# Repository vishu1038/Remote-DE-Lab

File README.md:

# Remote-DE-Lab
Remote Digital Electronics Lab

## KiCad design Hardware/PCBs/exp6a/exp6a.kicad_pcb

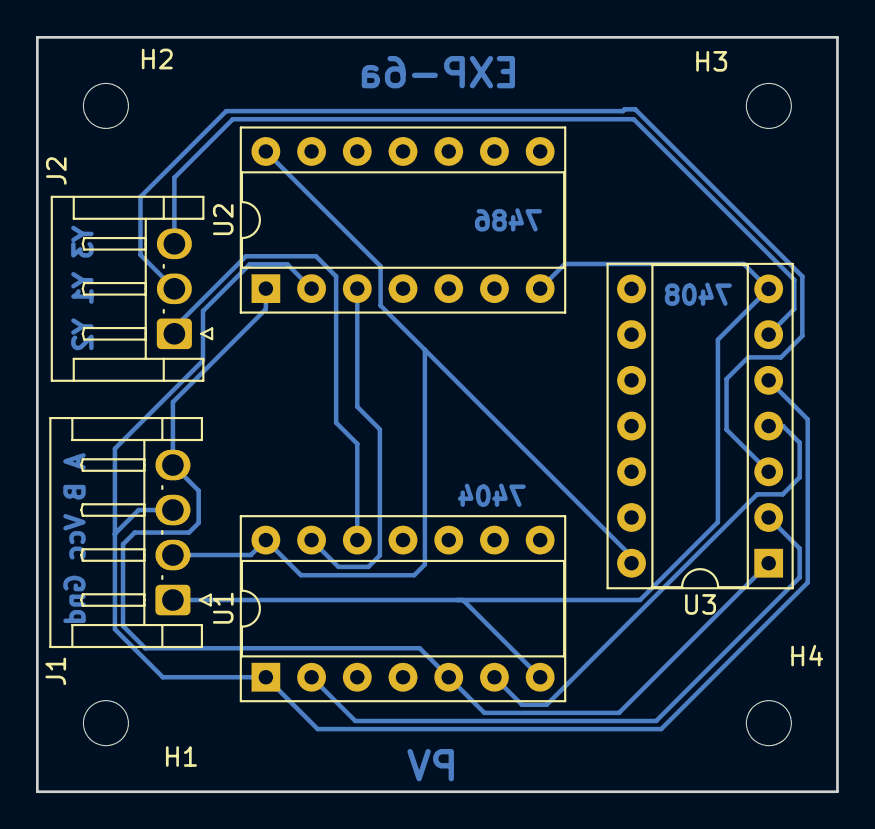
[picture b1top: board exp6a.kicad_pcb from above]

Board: 2 copper layers, 44.5 x 41.9 mm, 9 parts (0 on the bottom side), 10 nets.

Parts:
H1, H2, H3, H4: MountingHole; MountingHole_2.5mm
J1: A B Vcc Gnd; JST_EH_S4B-EH_1x04_P2.50mm_Horizontal
J2: Y3 Y1 Y2; JST_EH_S3B-EH_1x03_P2.50mm_Horizontal
U1: 7404; DIP-14_W7.62mm_Socket
U2: 7486; DIP-14_W7.62mm_Socket
U3: 7408; DIP-14_W7.62mm_Socket

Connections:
A: J1.4, U1.5, U2.1, U3.1
B: J1.3, U1.1, U2.2, U3.5
GND: J1.1, U1.7 (Gnd), U2.7 (Gnd), U3.7 (Gnd)
unnamed: U1.2, U3.2
unnamed: U1.6, U3.4
unnamed: U1.13, U2.3
VCC: J1.2, U1.14 (Vcc), U2.14 (Vcc), U3.14 (Vcc)
Y1: J2.2, U3.3
Y2: J2.1, U1.12
Y3: J2.3, U3.6

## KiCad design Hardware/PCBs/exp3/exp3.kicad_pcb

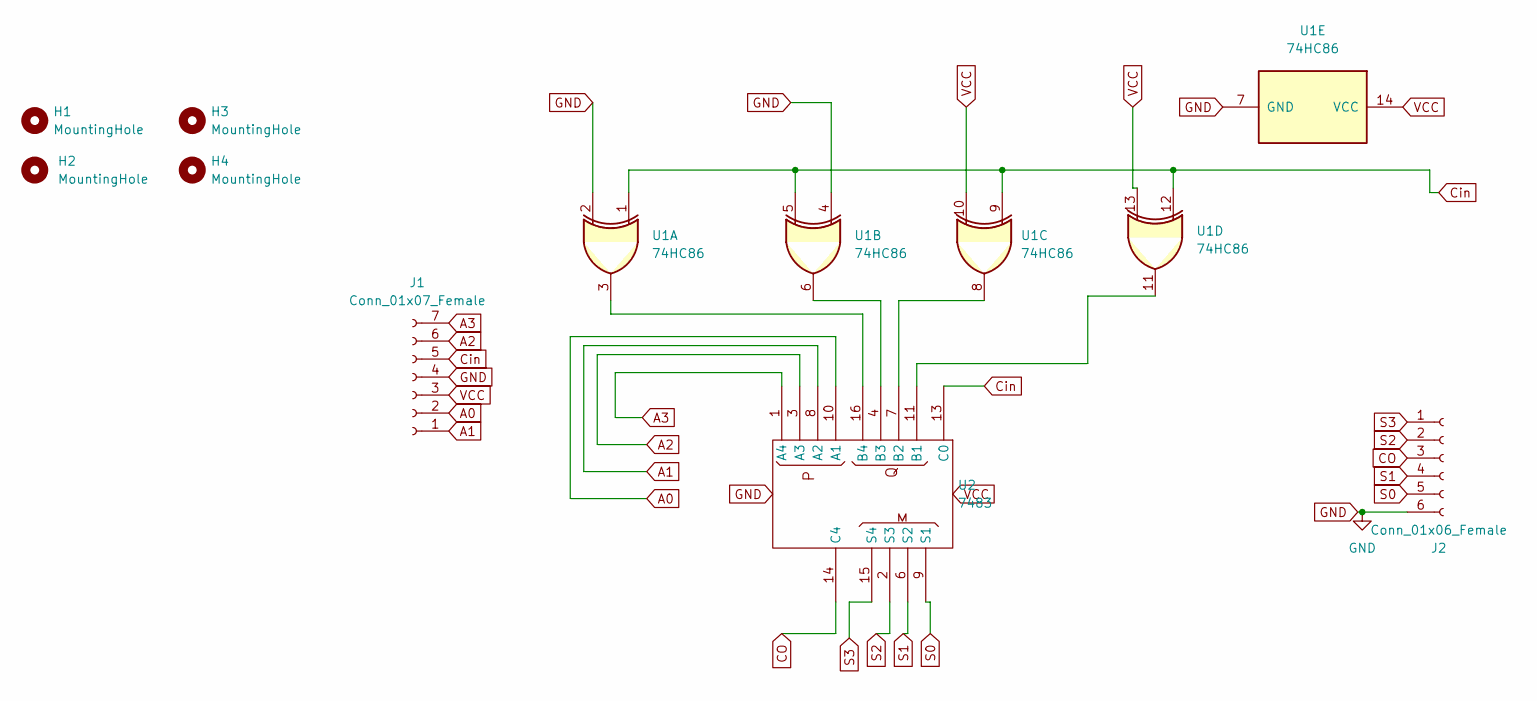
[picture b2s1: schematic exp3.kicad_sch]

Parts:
H1, H2, H3, H4: MountingHole; MountingHole_2.5mm
J1: Conn_01x07_Female; JST_EH_S7B-EH_1x07_P2.50mm_Horizontal
J2: Conn_01x06_Female; JST_EH_S6B-EH_1x06_P2.50mm_Horizontal
U1: 74HC86; DIP-14_W7.62mm_Socket
U2: 7483; DIP-16_W7.62mm_Socket

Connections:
A0: J1.2, U2.10 (A1)
A1: J1.1, U2.8 (A2)
A2: J1.6, U2.3 (A3)
A3: J1.7, U2.1 (A4)
CO: J2.3, U2.14 (C4)
Cin: J1.5, U1.1, U1.5, U1.9, U1.12, U2.13 (C0)
GND: J1.4, J2.6, U1.2, U1.4, U1.7 (GND), U2.12 (GND)
unnamed: U1.3, U2.16 (B4)
unnamed: U1.6, U2.4 (B3)
unnamed: U1.8, U2.7 (B2)
unnamed: U1.11, U2.11 (B1)
S0: J2.5, U2.9 (S1)
S1: J2.4, U2.6 (S2)
S2: J2.2, U2.2 (S3)
S3: J2.1, U2.15 (S4)
VCC: J1.3, U1.10, U1.13, U1.14 (VCC), U2.5 (VCC)

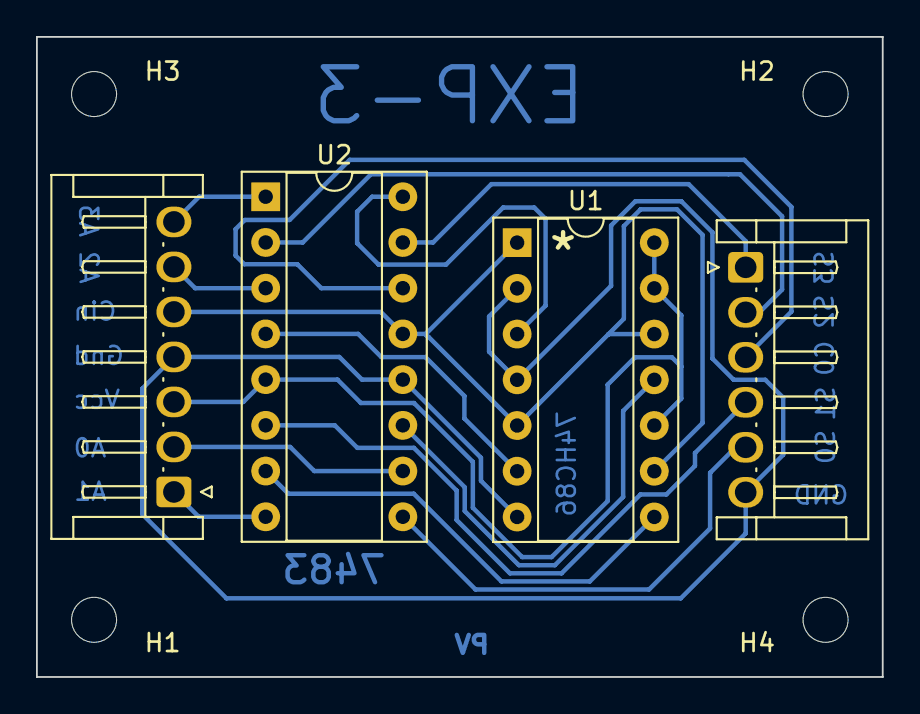
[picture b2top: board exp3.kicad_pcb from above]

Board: 2 copper layers, 47.0 x 35.6 mm, 8 parts (0 on the bottom side), 16 nets.

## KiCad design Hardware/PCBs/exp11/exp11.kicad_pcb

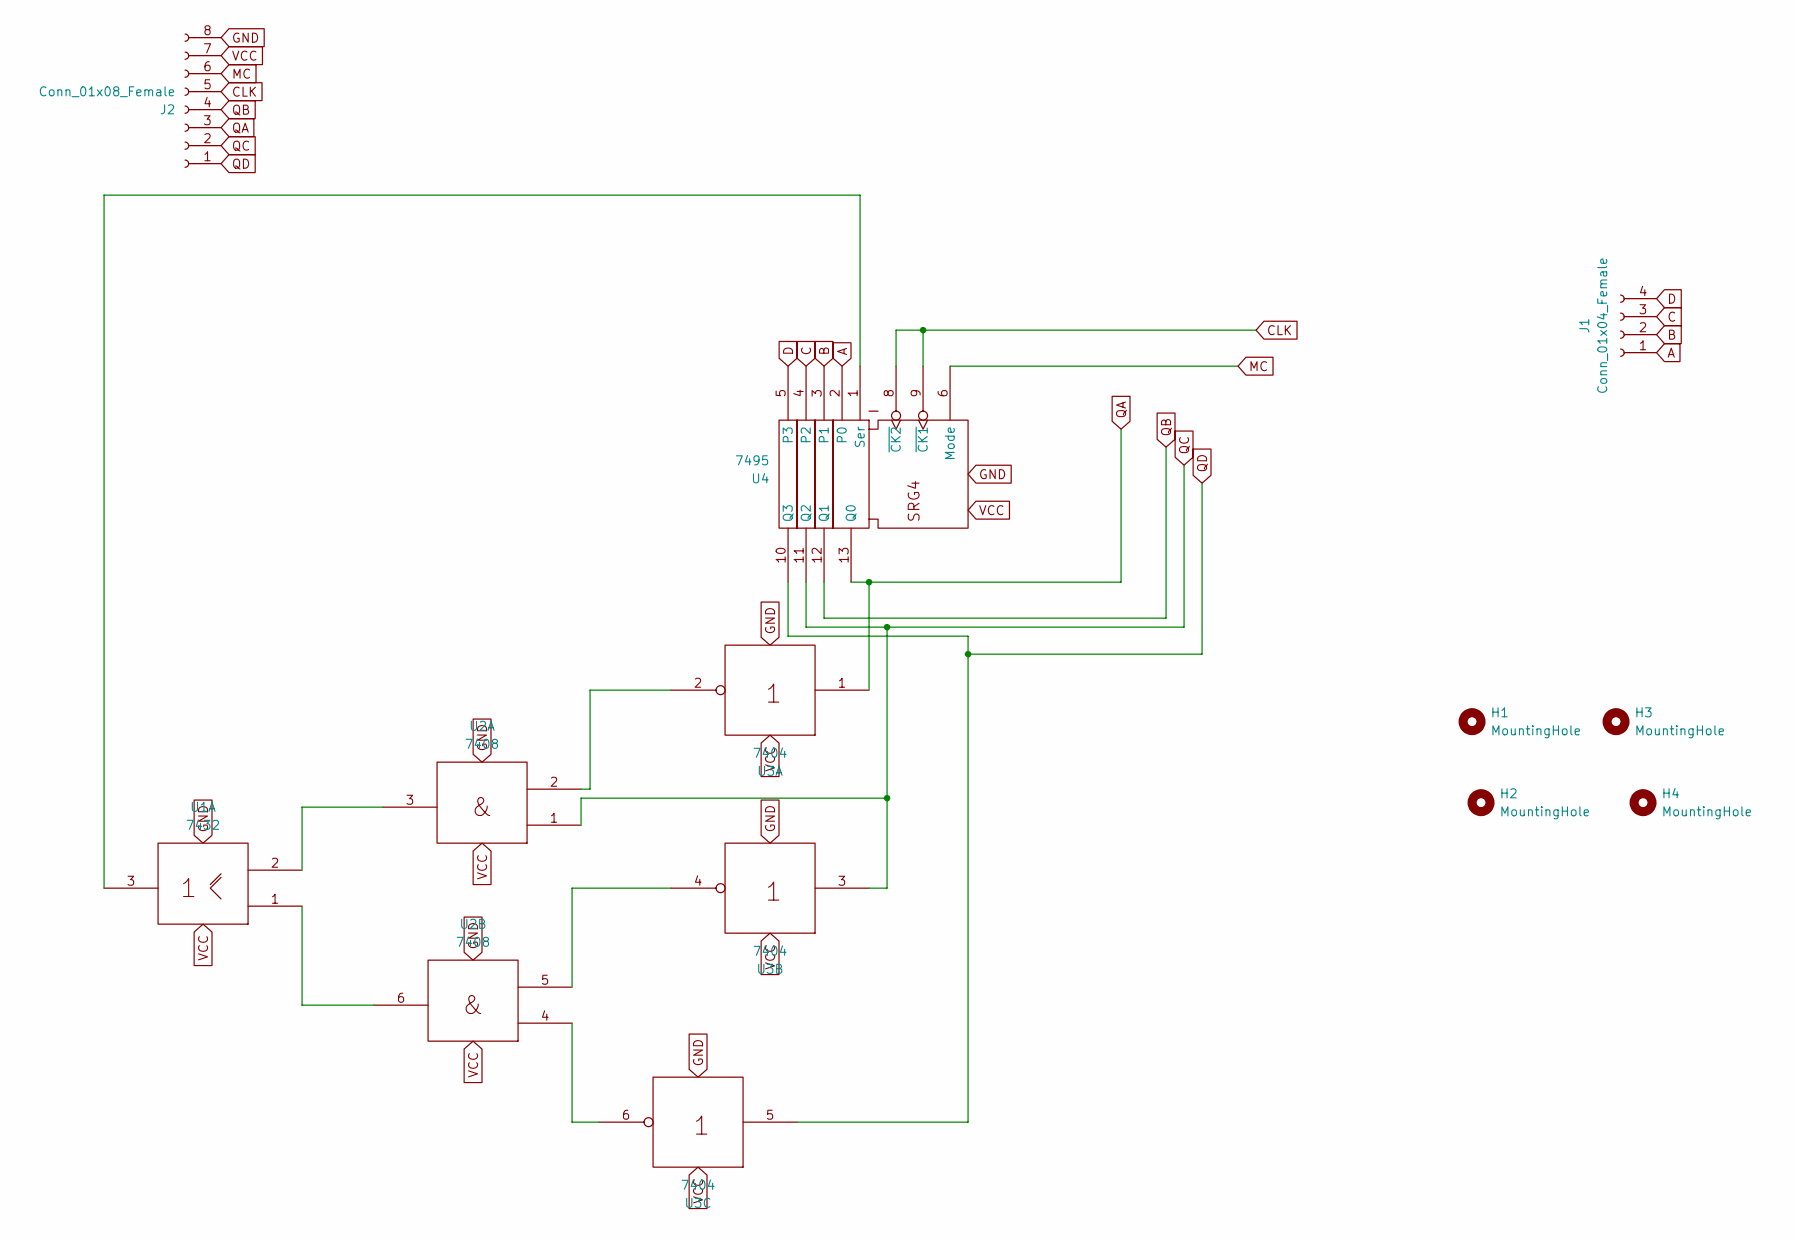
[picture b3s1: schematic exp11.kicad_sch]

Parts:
H1, H2, H3, H4: MountingHole; MountingHole_2.5mm
J1: Conn_01x04_Female; JST_EH_S4B-EH_1x04_P2.50mm_Horizontal
J2: Conn_01x08_Female; JST_EH_S8B-EH_1x08_P2.50mm_Horizontal
U1: 7432; DIP-14_W7.62mm_Socket
U2: 7408; DIP-14_W7.62mm_Socket
U3: 7404; DIP-14_W7.62mm_Socket
U4: 7495; DIP-14_W7.62mm_Socket

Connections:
A: J1.1, U4.2 (P0)
B: J1.2, U4.3 (P1)
C: J1.3, U4.4 (P2)
CLK: J2.5, U4.8 (~CK2), U4.9 (~CK1)
D: J1.4, U4.5 (P3)
GND: J2.8, U1.7 (Gnd), U2.7 (Gnd), U3.7 (Gnd), U4.7 (GND)
MC: J2.6, U4.6 (Mode)
unnamed: U1.1, U2.6
unnamed: U1.3, U4.1 (Ser)
unnamed: U2.2, U3.2
unnamed: U1.2, U2.3
unnamed: U2.4, U3.6
unnamed: U2.5, U3.4
QA: J2.3, U3.1, U4.13 (Q0)
QB: J2.4, U4.12 (Q1)
QC: J2.2, U2.1, U3.3, U4.11 (Q2)
QD: J2.1, U3.5, U4.10 (Q3)
VCC: J2.7, U1.14 (Vcc), U2.14 (Vcc), U3.14 (Vcc), U4.14 (VCC)

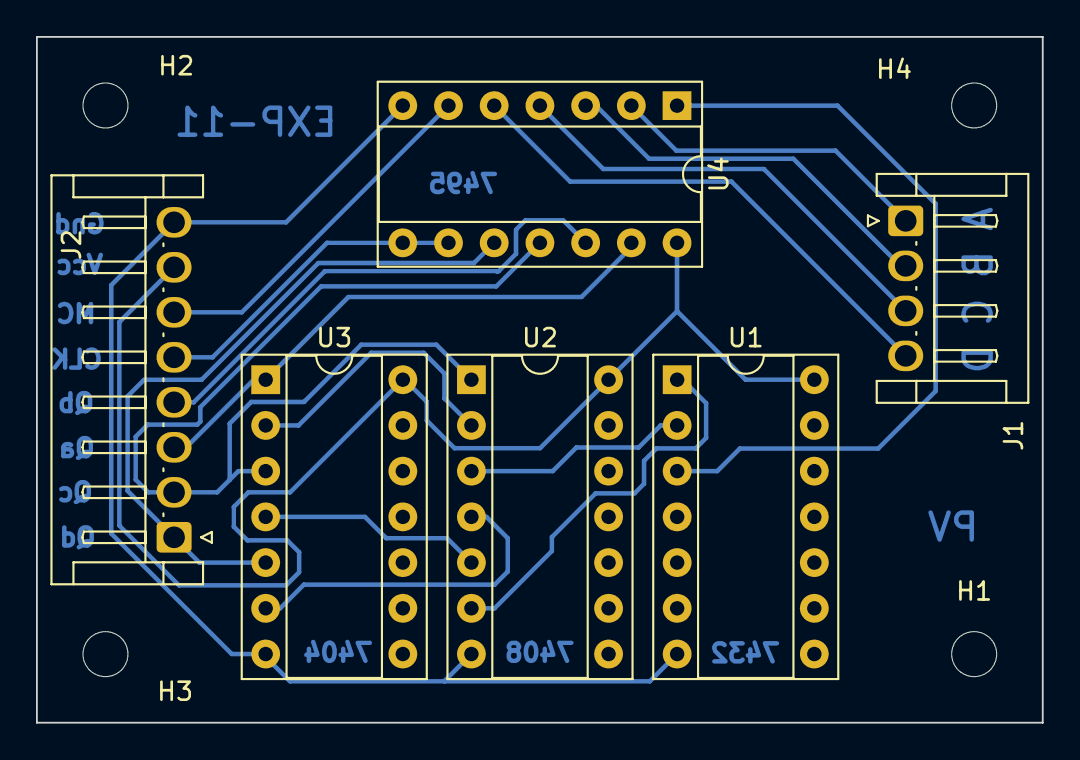
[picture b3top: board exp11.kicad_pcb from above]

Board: 2 copper layers, 55.9 x 38.1 mm, 10 parts (0 on the bottom side), 18 nets.

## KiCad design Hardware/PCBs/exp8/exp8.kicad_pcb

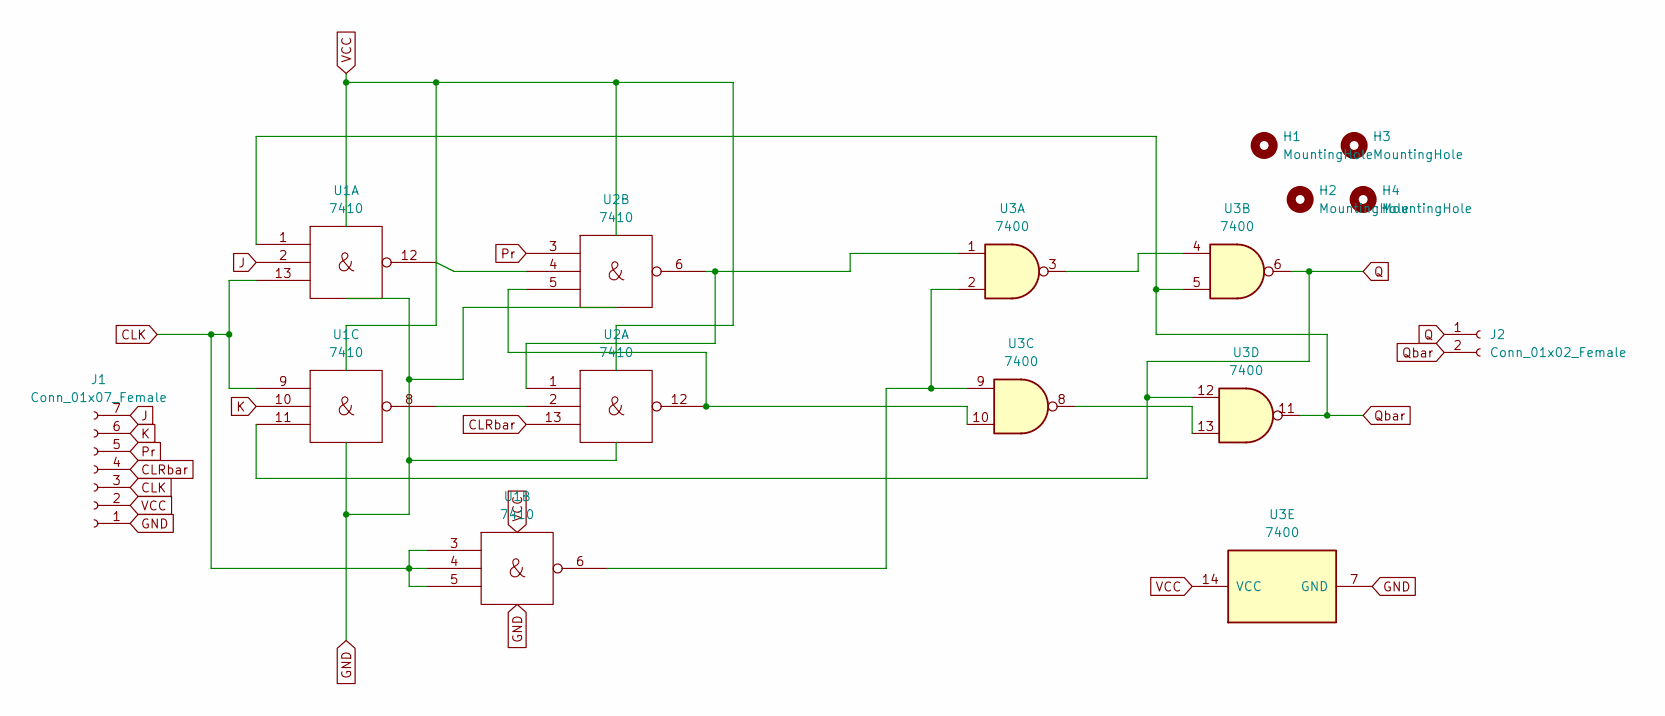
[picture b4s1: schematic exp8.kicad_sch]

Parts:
H1, H2, H3, H4: MountingHole; MountingHole_2.5mm
J1: Conn_01x07_Female; JST_EH_S7B-EH_1x07_P2.50mm_Horizontal
J2: Conn_01x02_Female; JST_EH_S2B-EH_1x02_P2.50mm_Horizontal
U1, U2: 7410; DIP-14_W7.62mm_Socket
U3: 7400; DIP-14_W7.62mm_Socket

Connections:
CLK: J1.3, U1.3, U1.4, U1.5, U1.9, U1.13
CLRbar: J1.4, U2.13
GND: J1.1, U1.7 (Gnd), U2.7 (Gnd), U3.7 (GND)
J: J1.7, U1.2
K: J1.6, U1.10
unnamed: U1.6, U3.2, U3.9
unnamed: U1.8, U2.2
unnamed: U1.12, U2.4
unnamed: U2.1, U2.6, U3.1
unnamed: U2.5, U2.12, U3.10
unnamed: U3.3, U3.4
unnamed: U3.8, U3.13
Pr: J1.5, U2.3
Q: J2.1, U1.11, U3.6, U3.12
Qbar: J2.2, U1.1, U3.5, U3.11
VCC: J1.2, U1.14 (Vcc), U2.14 (Vcc), U3.14 (VCC)

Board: 2 copper layers, 9 parts (0 on the bottom side), 16 nets, no tracks yet.

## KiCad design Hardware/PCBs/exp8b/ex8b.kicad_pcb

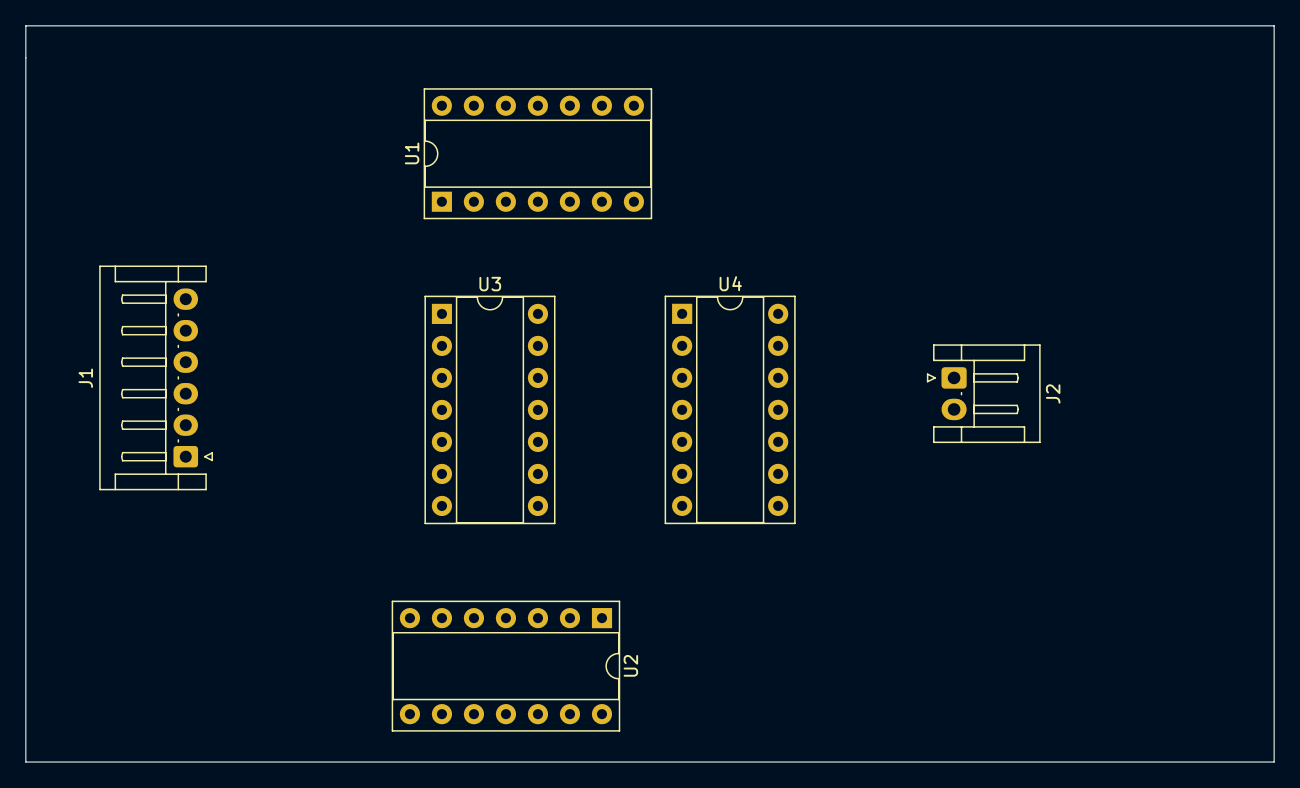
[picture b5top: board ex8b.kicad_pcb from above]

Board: 2 copper layers, 99.1 x 58.4 mm, 6 parts (0 on the bottom side), 16 nets, no tracks yet.

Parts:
J1: Conn_01x06_Female; JST_EH_S6B-EH_1x06_P2.50mm_Horizontal
J2: Conn_01x02_Female; JST_EH_S2B-EH_1x02_P2.50mm_Horizontal
U1, U2, U3: 7410; DIP-14_W7.62mm_Socket
U4: 7400; DIP-14_W7.62mm_Socket

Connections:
CLK: J1.3, U1.3, U1.4, U1.5, U1.9, U2.13
CLRbar: J1.4, U3.13
D: J1.6, U1.1, U1.2, U1.13, U2.2
GND: J1.1, U1.7 (Gnd), U2.7 (Gnd), U3.7 (Gnd), U4.7 (GND)
unnamed: U1.6, U4.2, U4.9
unnamed: U1.8, U3.2
unnamed: U1.10, U1.12
unnamed: U2.5, U3.12, U4.10
unnamed: U2.6, U3.1, U4.1
unnamed: U2.4, U2.12
unnamed: U4.3, U4.4
unnamed: U4.8, U4.13
Pr: J1.5, U2.3
Q: J2.1, U1.11, U4.6, U4.12
Qbar: J2.2, U2.1, U4.5, U4.11
VCC: J1.2, U1.14 (Vcc), U2.14 (Vcc), U3.14 (Vcc), U4.14 (VCC)

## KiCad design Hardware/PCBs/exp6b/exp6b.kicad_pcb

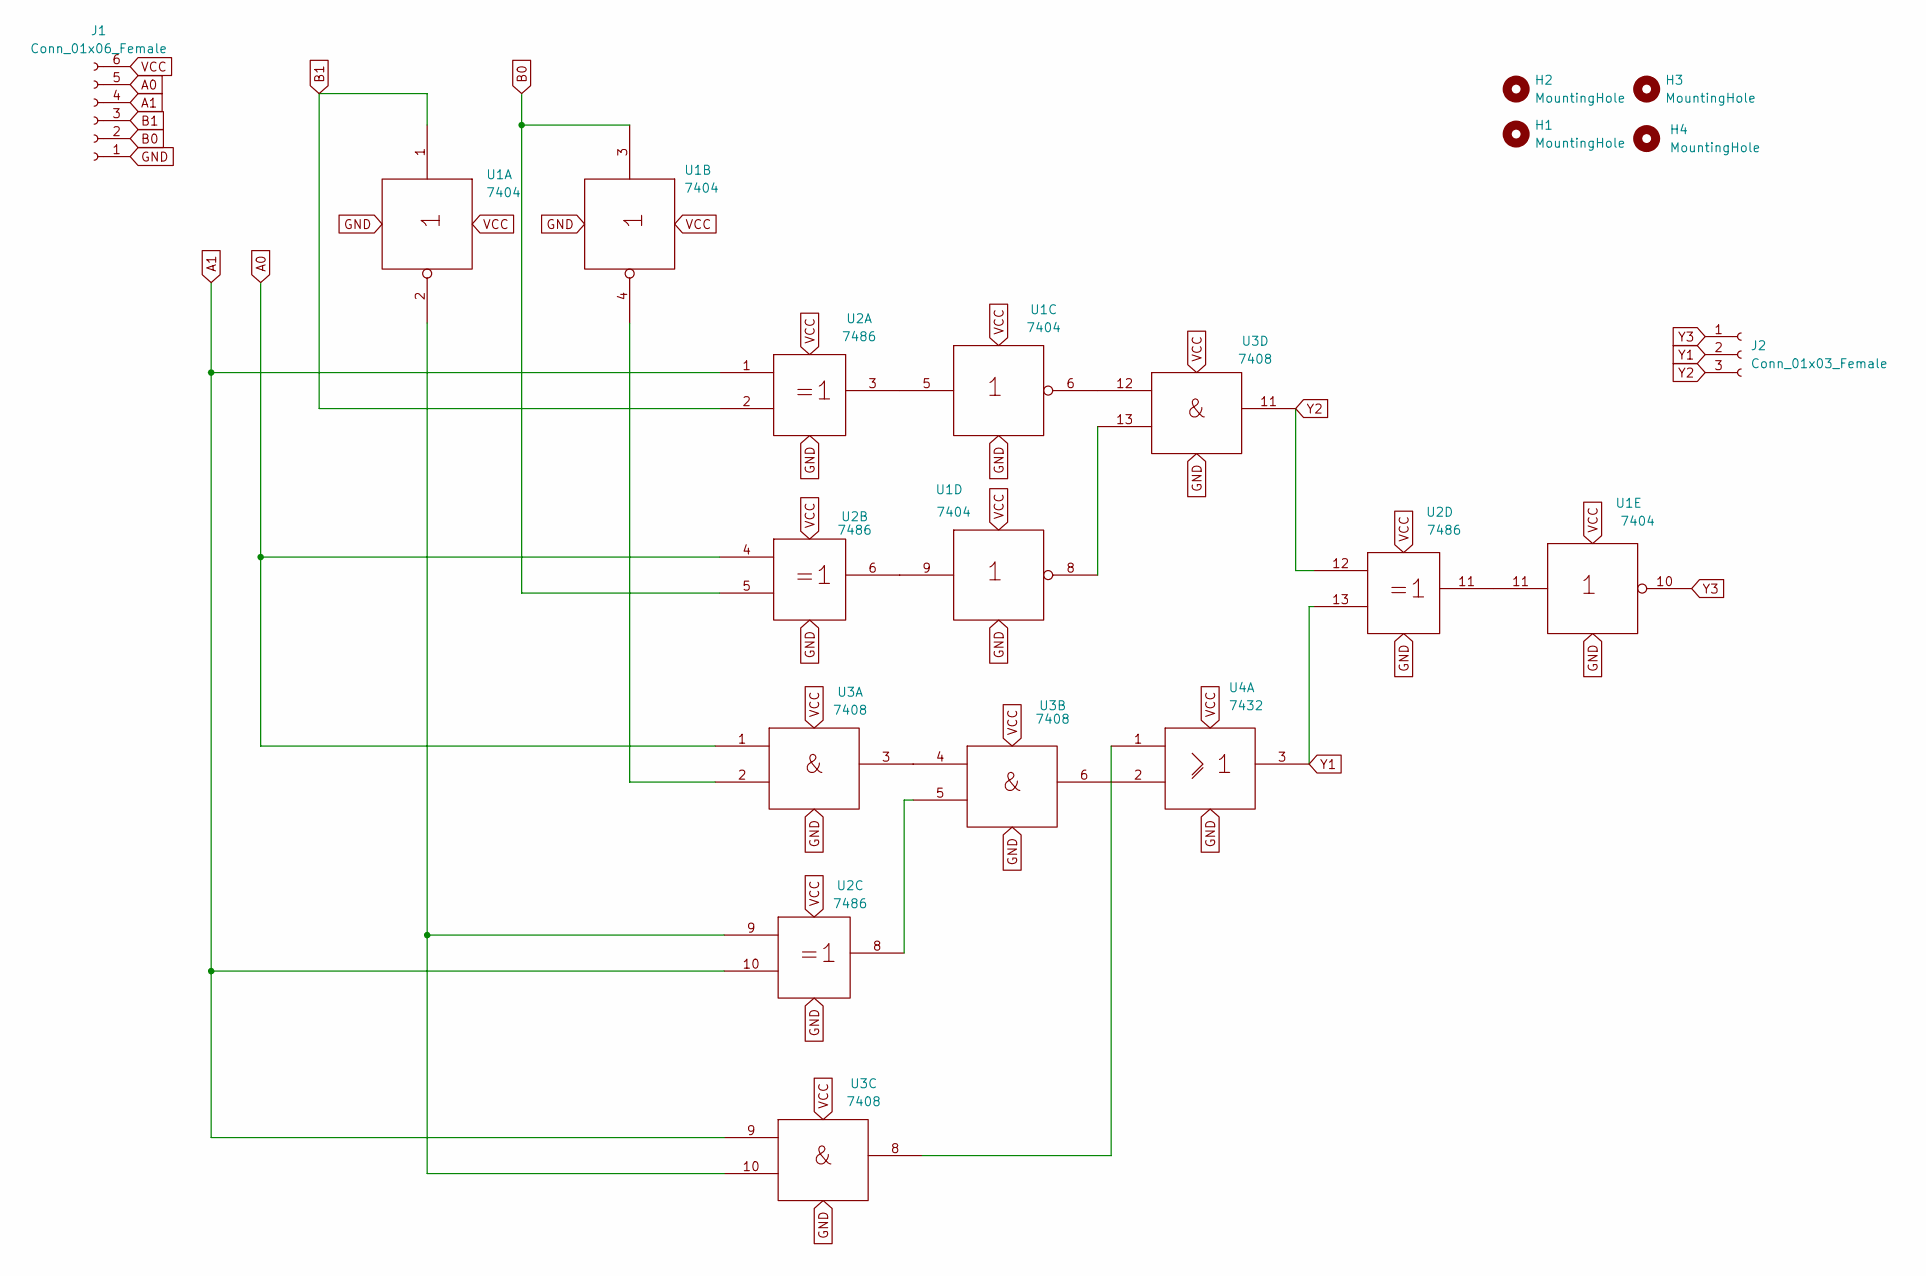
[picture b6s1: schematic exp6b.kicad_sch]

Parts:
H1, H2, H3, H4: MountingHole; MountingHole_2.5mm
J1: Conn_01x06_Female; JST_EH_S6B-EH_1x06_P2.50mm_Horizontal
J2: Conn_01x03_Female; JST_EH_S3B-EH_1x03_P2.50mm_Horizontal
U1: 7404; DIP-14_W7.62mm_Socket
U2: 7486; DIP-14_W7.62mm_Socket
U3: 7408; DIP-14_W7.62mm_Socket
U4: 7432; DIP-14_W7.62mm_Socket

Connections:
A0: J1.5, U2.4, U3.1
A1: J1.4, U2.1, U2.10, U3.9
B0: J1.2, U1.3, U2.5
B1: J1.3, U1.1, U2.2
GND: J1.1, U1.7 (Gnd), U2.7 (Gnd), U3.7 (Gnd), U4.7 (Gnd)
unnamed: U1.2, U2.9, U3.10
unnamed: U1.4, U3.2
unnamed: U1.6, U3.12
unnamed: U1.8, U3.13
unnamed: U1.5, U2.3
unnamed: U1.9, U2.6
unnamed: U2.8, U3.5
unnamed: U1.11, U2.11
unnamed: U3.3, U3.4
unnamed: U3.6, U4.2
unnamed: U3.8, U4.1
VCC: J1.6, U1.14 (Vcc), U2.14 (Vcc), U3.14 (Vcc), U4.14 (Vcc)
Y1: J2.2, U2.13, U4.3
Y2: J2.3, U2.12, U3.11
Y3: J2.1, U1.10

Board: 2 copper layers, 10 parts (0 on the bottom side), 20 nets, no tracks yet.

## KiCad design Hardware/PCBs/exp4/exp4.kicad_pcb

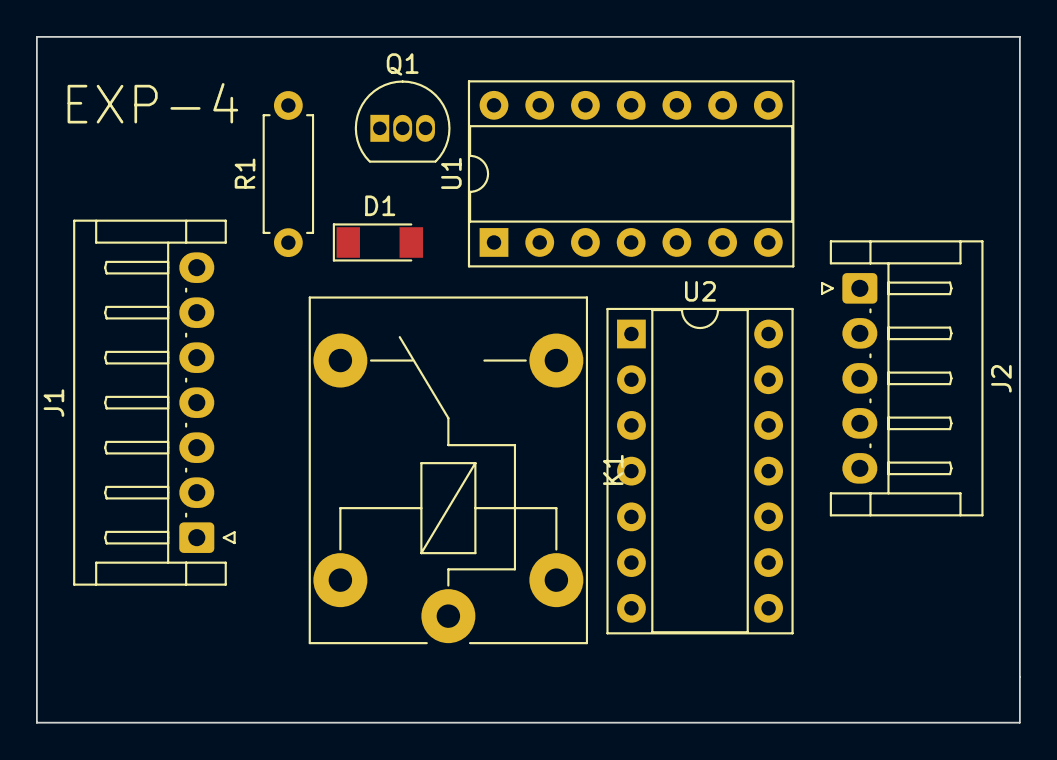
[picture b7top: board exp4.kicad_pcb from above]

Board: 2 copper layers, 54.6 x 38.1 mm, 8 parts (0 on the bottom side), 13 nets, no tracks yet.

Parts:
D1: DIODE; D_MiniMELF
J1: Conn_01x07_Female; JST_EH_S7B-EH_1x07_P2.50mm_Horizontal
J2: Conn_01x05_Female; JST_EH_S5B-EH_1x05_P2.50mm_Horizontal
K1: FINDER-36.11; Relay_SPDT_Finder_36.11
Q1: BC327; TO-92_Inline
R1: 1K; R_Axial_DIN0207_L6.3mm_D2.5mm_P7.62mm_Horizontal
U1, U2: 7486; DIP-14_W7.62mm_Socket

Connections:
B0: J1.4, U1.1, U2.10
B1: J1.5, U1.2, U1.4, U2.5
B2: J1.6, U1.5, U1.9, U2.2
B3: J1.7, J2.4, U1.10, U2.1
G0: J2.1, U1.3, U2.8
G1: J2.2, U1.6, U2.6, U2.9
G2: J2.3, U1.8, U2.3, U2.4
Gnd: D1.1 (A), J1.2, J2.5, K1.A2, U1.7 (Gnd), U2.7 (Gnd)
unnamed: D1.2 (K), K1.A1, Q1.1 (C)
unnamed: Q1.2 (B), R1.2
SEL: J1.3, R1.1
VCC: J1.1, K1.11, Q1.3 (E)
Vcc: K1.12, K1.14, U1.14 (Vcc), U2.14 (Vcc)

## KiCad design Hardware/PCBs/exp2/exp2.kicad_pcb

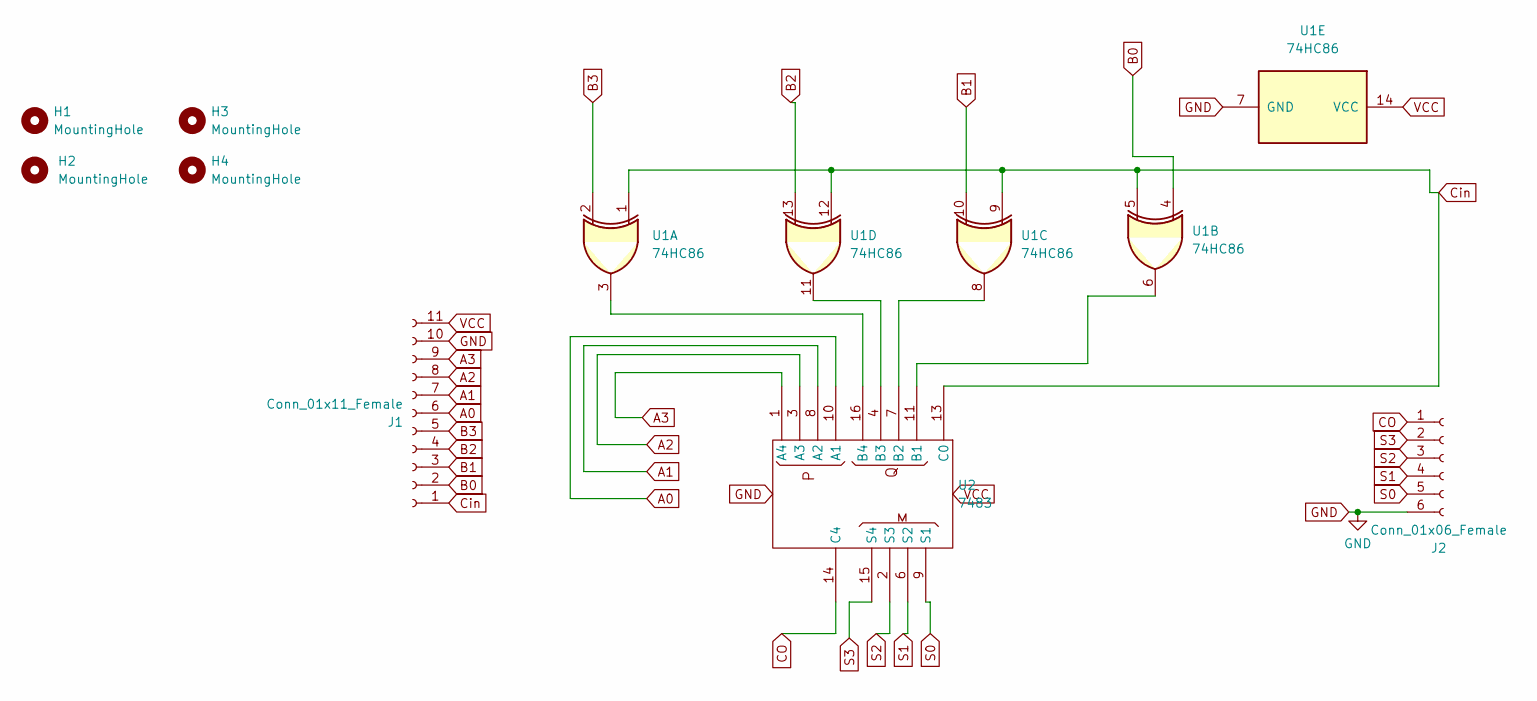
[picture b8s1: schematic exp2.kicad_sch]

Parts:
H1, H2, H3, H4: MountingHole; MountingHole_2.5mm
J1: Conn_01x11_Female; JST_EH_S11B-EH_1x11_P2.50mm_Horizontal
J2: Conn_01x06_Female; JST_EH_S6B-EH_1x06_P2.50mm_Horizontal
U1: 74HC86; DIP-14_W7.62mm_Socket
U2: 7483; DIP-16_W7.62mm_Socket

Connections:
A0: J1.6, U2.10 (A1)
A1: J1.7, U2.8 (A2)
A2: J1.8, U2.3 (A3)
A3: J1.9, U2.1 (A4)
B0: J1.2, U1.4
B1: J1.3, U1.10
B2: J1.4, U1.13
B3: J1.5, U1.2
CO: J2.1, U2.14 (C4)
Cin: J1.1, U1.1, U1.5, U1.9, U1.12, U2.13 (C0)
GND: J1.10, J2.6, U1.7 (GND), U2.12 (GND)
unnamed: U1.3, U2.16 (B4)
unnamed: U1.6, U2.11 (B1)
unnamed: U1.8, U2.7 (B2)
unnamed: U1.11, U2.4 (B3)
S0: J2.5, U2.9 (S1)
S1: J2.4, U2.6 (S2)
S2: J2.3, U2.2 (S3)
S3: J2.2, U2.15 (S4)
VCC: J1.11, U1.14 (VCC), U2.5 (VCC)

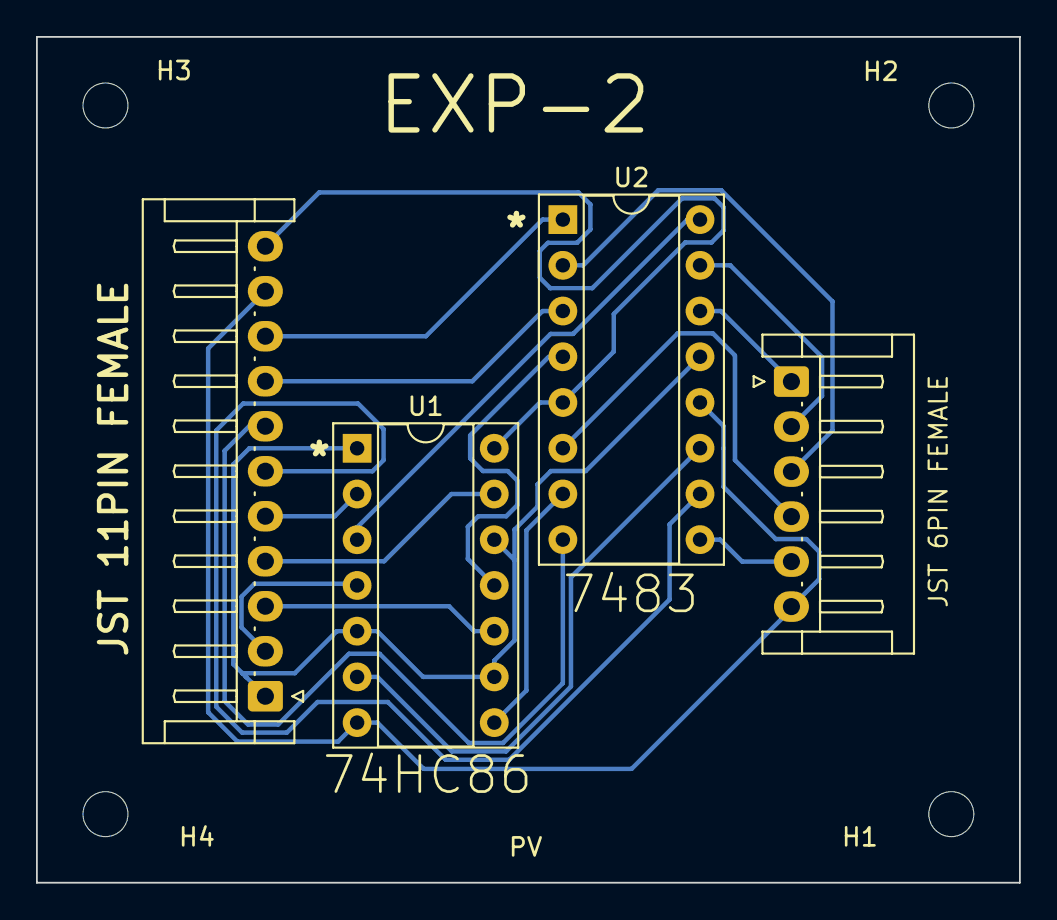
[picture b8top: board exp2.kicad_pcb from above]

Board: 2 copper layers, 54.6 x 47.0 mm, 8 parts (0 on the bottom side), 20 nets.

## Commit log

2022-10-10 PCBs and Lab Manual
    PCBs and lab manual uploaded
2022-10-10 PCBs Updated
    pcb of exp1, 2 and 3 updated
2022-10-14 Exp - 2 and 3 PCB Updated
2022-10-17 Several PCBs updated
2022-10-17 basic ESP Web Server created
2022-11-11 exp 3 PCB updated
2022-11-11 updated exp 6a PCB
2022-11-14 Basic Web Server Completed
2022-11-14 Multiple PCBs updated
2022-11-15 exp1 added to server
2022-12-09 PCBs Updated
2022-12-09 Modularized code and added more experiments
2022-12-09 Added IO Expander and more modularization
2022-12-10 Added Exp 3
2022-12-10 Added Exp 6a
2022-12-10 Added exp 11 and updated pins
